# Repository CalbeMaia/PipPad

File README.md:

# PipPad
A hackpad inspired by Fallout's hardware

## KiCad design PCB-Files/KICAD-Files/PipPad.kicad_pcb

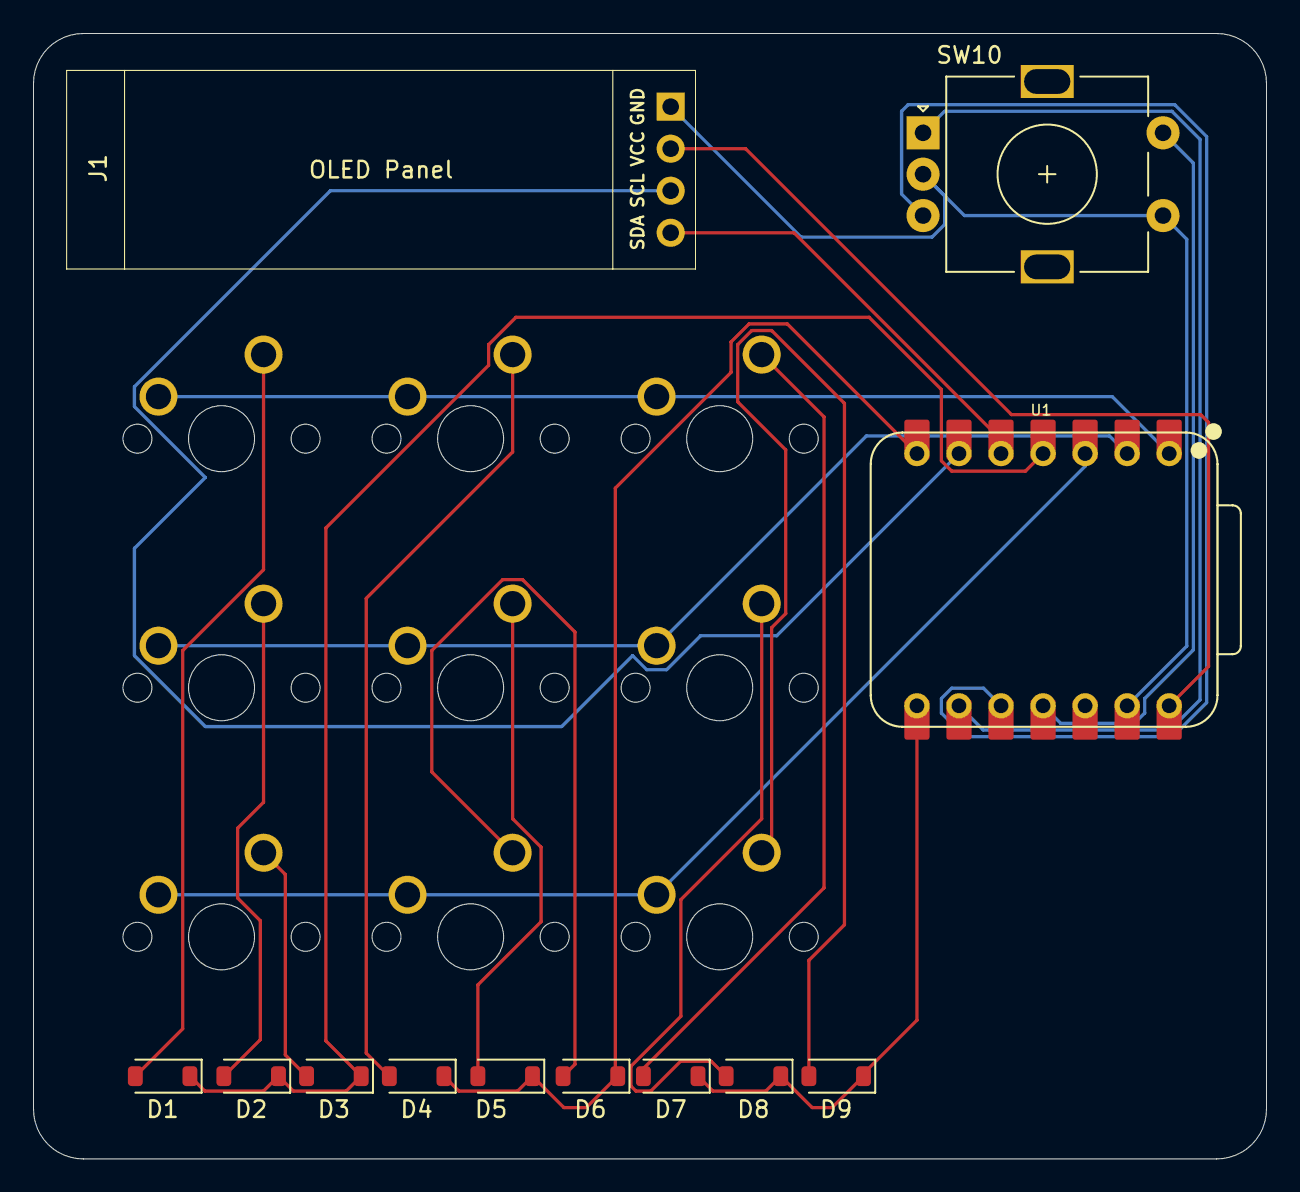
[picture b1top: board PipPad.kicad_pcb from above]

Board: 2 copper layers, 74.5 x 68.0 mm, 21 parts (0 on the bottom side), 22 nets.

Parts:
D1, D2, D3, D4, D5, D6, D7, D8, D9: 1N4148; D_SOD-123
J1: Conn_01x04_Socket; SSD1306-0.91-OLED-4pin-128x32
SW1, SW2, SW3, SW4, SW5, SW6, SW7, SW8, SW9: SW_Push; SW_MX_1u
SW10: RotaryEncoder_Switch; RotaryEncoder_Alps_EC11E-Switch_Vertical_H20mm
U1: MOUDLE-SEEEDUINO-XIAO; XIAO-RP2040-DIP

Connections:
/Col1: SW1.1, SW4.1, SW7.1, U1.1 (PA02_A0_D0)
/Col2: SW2.1, SW5.1, SW8.1, U1.2 (PA4_A1_D1)
/Col3: SW3.1, SW6.1, SW9.1, U1.3 (PA10_A2_D2)
/Row1: D1.1 (K), D2.1 (K), D3.1 (K), U1.4 (PA11_A3_D3)
/Row2: D4.1 (K), D5.1 (K), D6.1 (K), U1.7 (PB08_A6_D6_TX)
/Row3: D7.1 (K), D8.1 (K), D9.1 (K), U1.8 (PB09_A7_D7_RX)
GND: J1.1, SW10.C, SW10.S1, U1.13 (GND)
unnamed: D1.2 (A), SW1.2
unnamed: D2.2 (A), SW2.2
unnamed: D3.2 (A), SW3.2
unnamed: D4.2 (A), SW4.2
unnamed: D5.2 (A), SW5.2
unnamed: D6.2 (A), SW6.2
unnamed: D7.2 (A), SW7.2
unnamed: D8.2 (A), SW8.2
unnamed: D9.2 (A), SW9.2
unnamed: J1.3, U1.6 (PA9_A5_D5_SCL)
unnamed: J1.4, U1.5 (PA8_A4_D4_SDA)
unnamed: SW10.B, U1.10 (PA5_A9_D9_MISO)
unnamed: SW10.S2, U1.11 (PA6_A10_D10_MOSI)
unnamed: SW10.A, U1.9 (PA7_A8_D8_SCK)
VCC: J1.2, U1.14 (5V)

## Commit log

2026-04-14 Create Case-CAD
2026-04-14 Create Gerber+Drill-Files
